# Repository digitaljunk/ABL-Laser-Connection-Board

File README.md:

# ABL-Laser-Connection-Board
https://www.thingiverse.com/thing:2757972

This circuit board provides ABL and Laser functionally trough a 6 wire cable to the print head. It's designed for laser modules with separate 5V PWM and 12V work voltage

It also brings down the 12V PWM signal from the part cooling fan to 5V PWM to
connect the laser module PWM/TTL port.
It provides a 12V work voltage with the ability to add a safety switch to prevent laser operation during printer start up. You can also add door switches or an emergency switch so secure the laser operation.
You can optionally connect an external power supply for the laser and ABL sensor.
The board provides an optocoupler for the ABL sensor.
All connections are provided via an 6-pin connector to the print head.

You can mount the PCB to the printer frame with 3mm bolds and headnuts near the Z stepper.

Feel free to provide a nice and snugly printable case. You can bend the LED to point upwards the PCB.

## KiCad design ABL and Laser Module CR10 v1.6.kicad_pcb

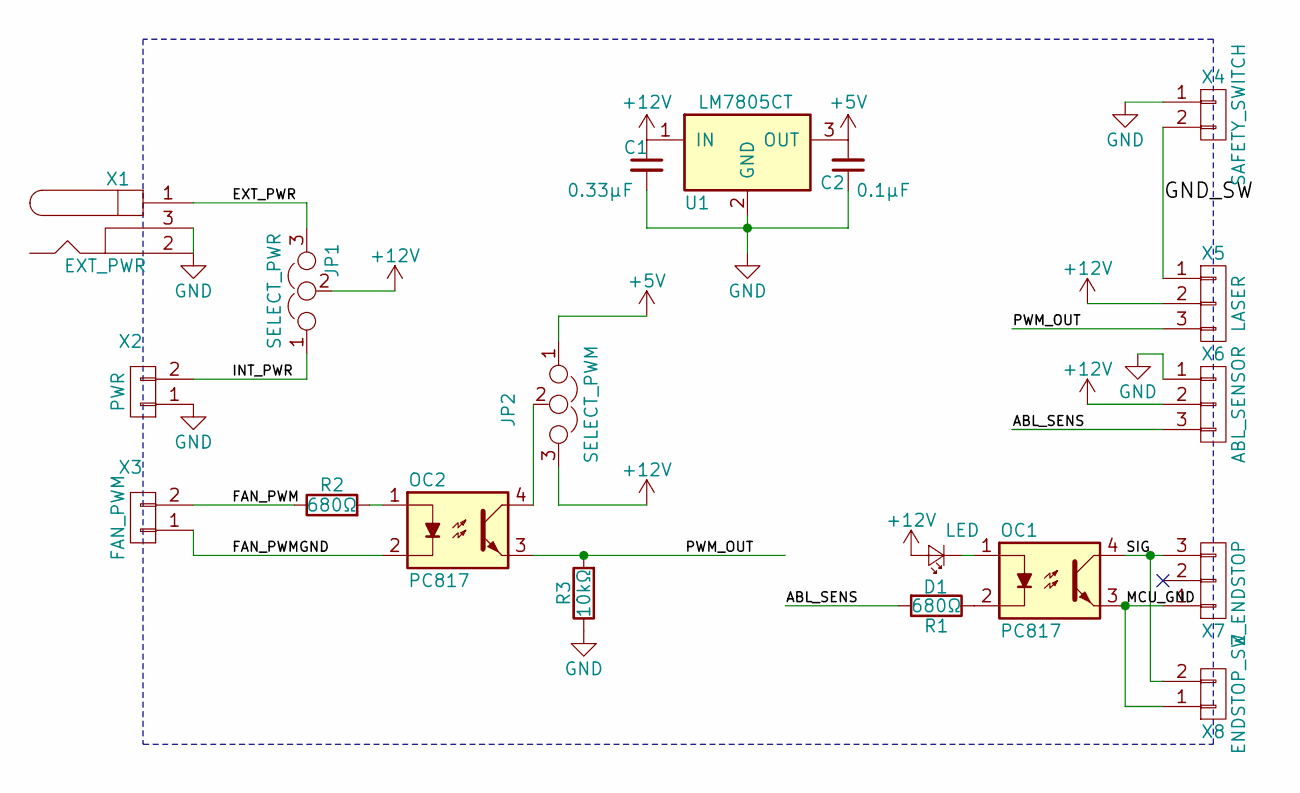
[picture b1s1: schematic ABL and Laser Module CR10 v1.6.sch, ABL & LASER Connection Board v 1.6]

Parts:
C1: 0.33µF; C_Disc_D5.0mm_W2.5mm_P5.00mm
C2: 0.1µF; C_Disc_D5.0mm_W2.5mm_P5.00mm
D1: LED; LED_D3.0mm
JP1: SELECT_PWR; Pin_Header_Straight_1x03_Pitch2.54mm
JP2: SELECT_PWM; Pin_Header_Straight_1x03_Pitch2.54mm
OC1, OC2: PC817; DIP-4_W7.62mm
R1, R2: 680Ω; R_Axial_DIN0207_L6.3mm_D2.5mm_P7.62mm_Horizontal
R3: 10kΩ; R_Axial_DIN0207_L6.3mm_D2.5mm_P7.62mm_Horizontal
U1: LM7805CT; TO-220-3_Horizontal_thermal
X1: EXT_PWR; Barrel_Jack_CUI_PJ-102AH
X2: PWR; JST_XH_S02B-XH-A_02x2.50mm_Angled
X3: FAN_PWM; JST_XH_S02B-XH-A_02x2.50mm_Angled
X4: SAFETY_SWITCH; JST_XH_S02B-XH-A_02x2.50mm_Angled
X5: LASER; JST_XH_S03B-XH-A_03x2.50mm_Angled
X6: ABL_SENSOR; JST_XH_S03B-XH-A_03x2.50mm_Angled
X7: Z_ENDSTOP; JST_XH_S03B-XH-A_03x2.50mm_Angled
X8: ENDSTOP_SW; JST_XH_S02B-XH-A_02x2.50mm_Angled

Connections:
+5V: C2.2, JP2.1, U1.3 (OUT)
+12V: C1.1, D1.2 (A), JP1.2, JP2.3, U1.1 (IN), X5.2, X6.2
/ABL_SENS: R1.2, X6.3
/EXT_PWR: JP1.3, X1.1
/FAN_PWM: R2.1, X3.2
/FAN_PWMGND: OC2.2, X3.1
/GND_SW: X4.2, X5.1
/INT_PWR: JP1.1, X2.2
/MCU_GND: OC1.3, X7.1, X8.1
/PWM_OUT: OC2.3, R3.2, X5.3
/SIG: OC1.4, X7.3, X8.2
GND: C1.2, C2.1, R3.1, U1.2 (GND), X1.2, X1.3, X2.1, X4.1, X6.1
unnamed: D1.1 (K), OC1.1
unnamed: JP2.2, OC2.4
unnamed: OC1.2, R1.1
unnamed: OC2.1, R2.2

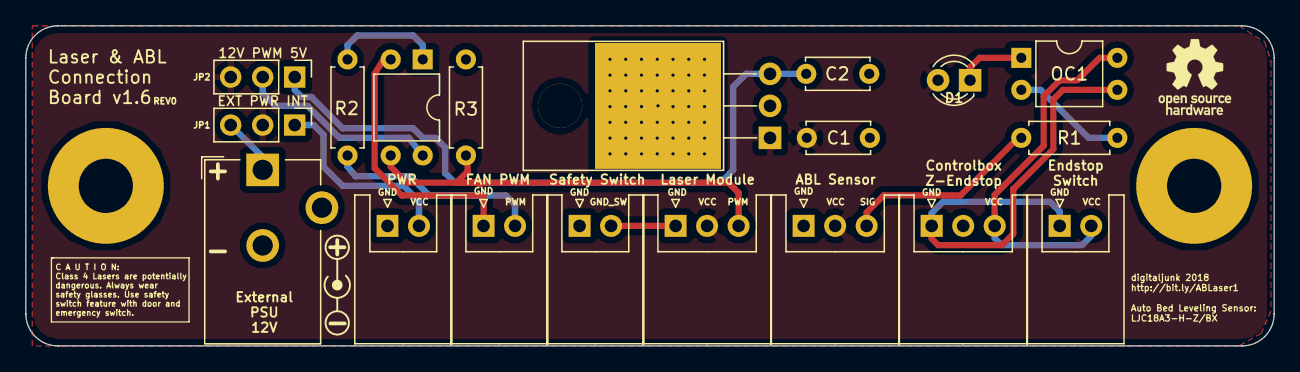
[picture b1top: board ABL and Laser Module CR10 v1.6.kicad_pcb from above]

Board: 2 copper layers, 99.1 x 25.4 mm, 19 parts (0 on the bottom side), 16 nets.

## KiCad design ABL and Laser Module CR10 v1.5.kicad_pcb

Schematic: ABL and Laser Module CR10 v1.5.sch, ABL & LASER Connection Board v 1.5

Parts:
C1: 0.33µF; C_Disc_D5.0mm_W2.5mm_P5.00mm
C2: 0.1µF; C_Disc_D5.0mm_W2.5mm_P5.00mm
D1: LED; LED_D3.0mm
EXT_PWR_IN1: BARREL_JACK; Barrel_Jack_CUI_PJ-102AH
EndStopIN1: JST_XH_2; JST_XH_S02B-XH-A_02x2.50mm_Angled
EndStopOut1: JST_XH_3; JST_XH_S03B-XH-A_03x2.50mm_Angled
HEAD0: JST_XH_6; JST_XH_S06B-XH-A_06x2.50mm_Angled
J1: CONN_01X04; JST_XH_S04B-XH-A_04x2.50mm_Angled
J2: CONN_01X06; JST_XH_S06B-XH-A_06x2.50mm_Angled
J3: CONN_01X03; JST_XH_S03B-XH-A_03x2.50mm_Angled
JP1: Jumper_NC_Dual; Pin_Header_Straight_1x03_Pitch2.54mm
OC1: PC817; DIP-4_W7.62mm
PWM/PWR_IN1: JST_XH_4; JST_XH_S04B-XH-A_04x2.50mm_Angled
R1: 680Ω; R_Axial_DIN0207_L6.3mm_D2.5mm_P7.62mm_Horizontal
SAFETY_SW1: JST_XH_2; JST_XH_S02B-XH-A_02x2.50mm_Angled
U1: LM7805CT; TO-220-3_Horizontal_thermal

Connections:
GND: C1.2, C2.1, HEAD0.4, PWM/PWR_IN1.3, U1.2 (GND)
unnamed: C1.1, JP1.1, PWM/PWR_IN1.4, U1.1 (IN)
unnamed: C2.2, JP1.3, U1.3 (OUT)
unnamed: D1.1 (K), OC1.1
unnamed: D1.2 (A), EXT_PWR_IN1.1, HEAD0.1, PWM/PWR_IN1.1, SAFETY_SW1.1
unnamed: EXT_PWR_IN1.2, EXT_PWR_IN1.3, HEAD0.3, PWM/PWR_IN1.2
unnamed: EndStopIN1.1, EndStopOut1.1, OC1.4
unnamed: EndStopIN1.2, EndStopOut1.3, OC1.3
unnamed: HEAD0.2, R1.2
unnamed: HEAD0.5, JP1.2
unnamed: HEAD0.6, SAFETY_SW1.2
unnamed: J1.1, J2.6
unnamed: J1.2, J2.5
unnamed: J1.3, J2.4
unnamed: J1.4, J2.3, J3.1
unnamed: J2.1, J3.3
unnamed: J2.2, J3.2
unnamed: OC1.2, R1.1

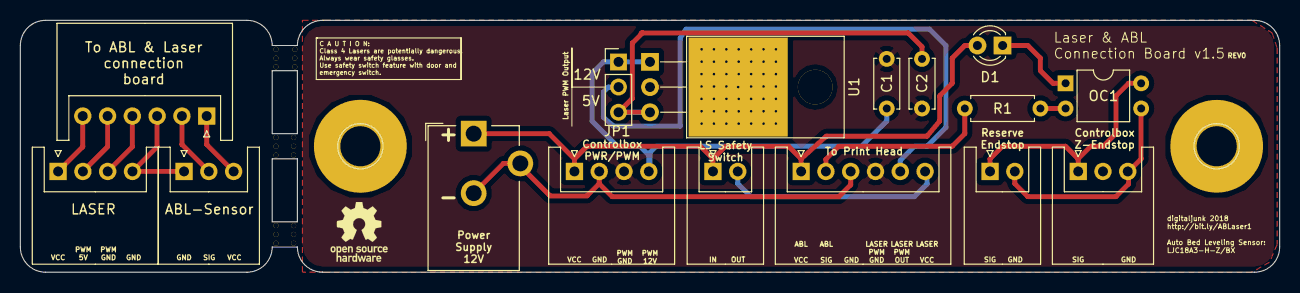
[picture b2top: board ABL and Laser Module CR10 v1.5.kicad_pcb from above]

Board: 2 copper layers, 127.0 x 25.4 mm, 17 parts (1 on the bottom side), 18 nets.

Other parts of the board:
OSHW_COPPER_10MM: VAL**; OSHW_COPPER_10MM

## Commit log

2018-02-13 v1.6 commit
2018-07-06 Update README.md
    Description added
